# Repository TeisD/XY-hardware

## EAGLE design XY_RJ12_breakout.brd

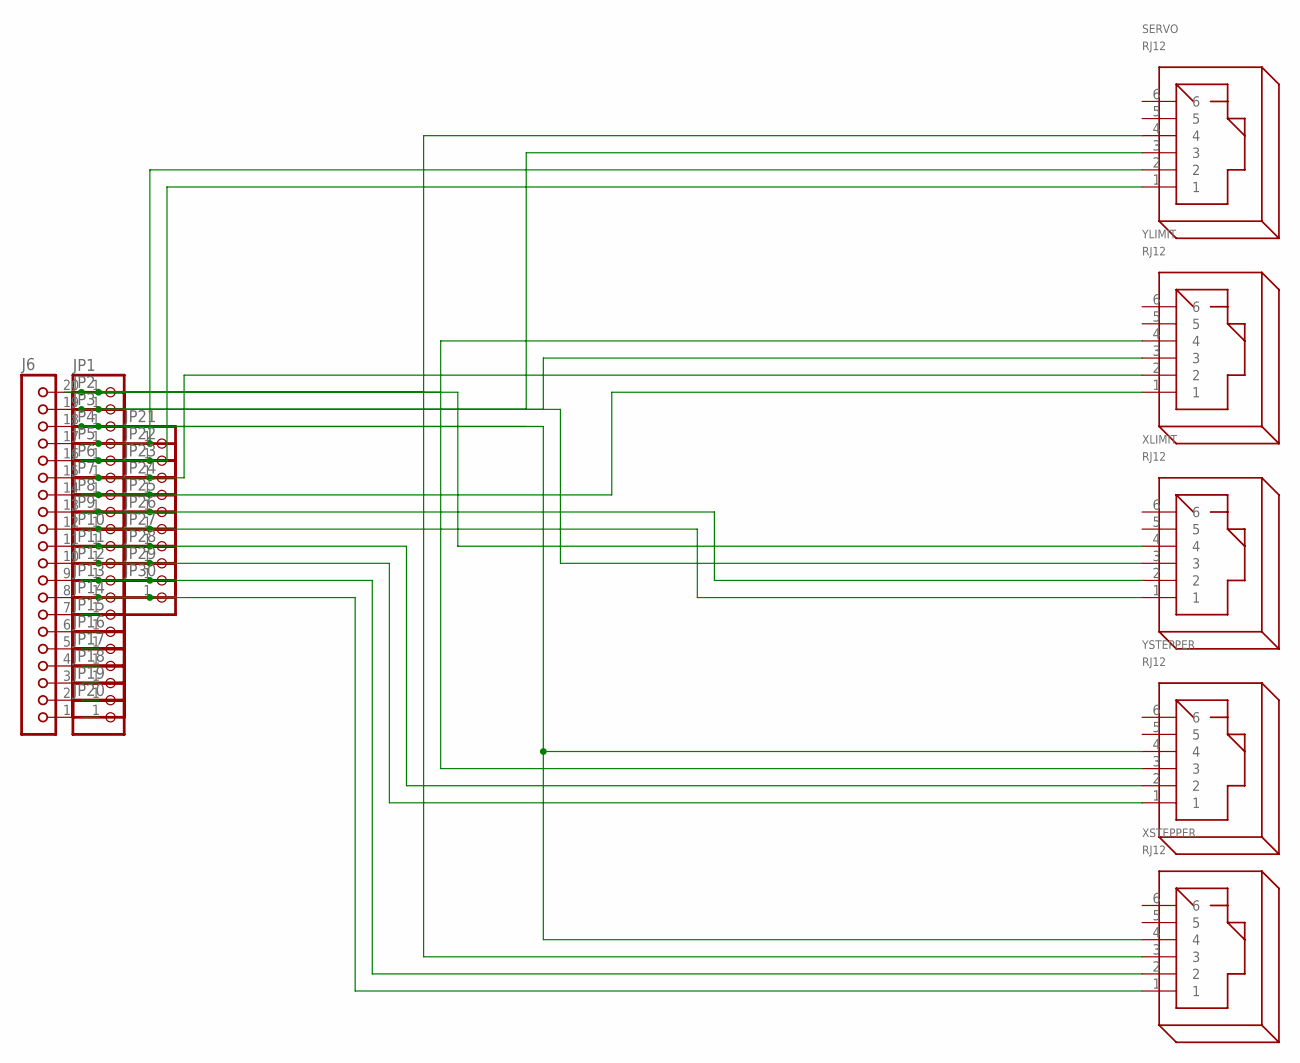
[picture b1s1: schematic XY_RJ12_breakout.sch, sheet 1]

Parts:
J6: JBK20
JP1, JP2, JP3, JP4, JP5, JP6, JP7, JP8, JP9, JP10, JP11, JP12, JP13, JP14, JP15, JP16, JP17, JP18, JP19, JP20, JP21, JP22, JP23, JP24, JP25, JP26, JP27, JP28, JP29, JP30: PINHD-1X1; 1X01
SERVO: RJ12
XLIMIT: RJ12
XSTEPPER: RJ12
YLIMIT: RJ12
YSTEPPER: RJ12

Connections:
unnamed: J6.20, JP1.1, SERVO.4, XLIMIT.4, XSTEPPER.3, YLIMIT.4, YSTEPPER.3
unnamed: J6.19, JP2.1, SERVO.3, XLIMIT.3, YLIMIT.3
unnamed: J6.18, JP3.1, XSTEPPER.4, YSTEPPER.4
unnamed: J6.17, JP4.1, JP21.1, SERVO.2
unnamed: J6.16, JP5.1, JP22.1, SERVO.1
unnamed: J6.15, JP6.1, JP23.1, YLIMIT.2
unnamed: J6.14, JP7.1, JP24.1, YLIMIT.1
unnamed: J6.13, JP8.1, JP25.1, XLIMIT.2
unnamed: J6.12, JP9.1, JP26.1, XLIMIT.1
unnamed: J6.11, JP10.1, JP27.1, YSTEPPER.2
unnamed: J6.10, JP11.1, JP28.1, YSTEPPER.1
unnamed: J6.9, JP12.1, JP29.1, XSTEPPER.2
unnamed: J6.8, JP13.1, JP30.1, XSTEPPER.1
unnamed: J6.1, JP20.1
unnamed: J6.2, JP19.1
unnamed: J6.3, JP18.1
unnamed: J6.4, JP17.1
unnamed: J6.5, JP16.1
unnamed: J6.6, JP15.1
unnamed: J6.7, JP14.1

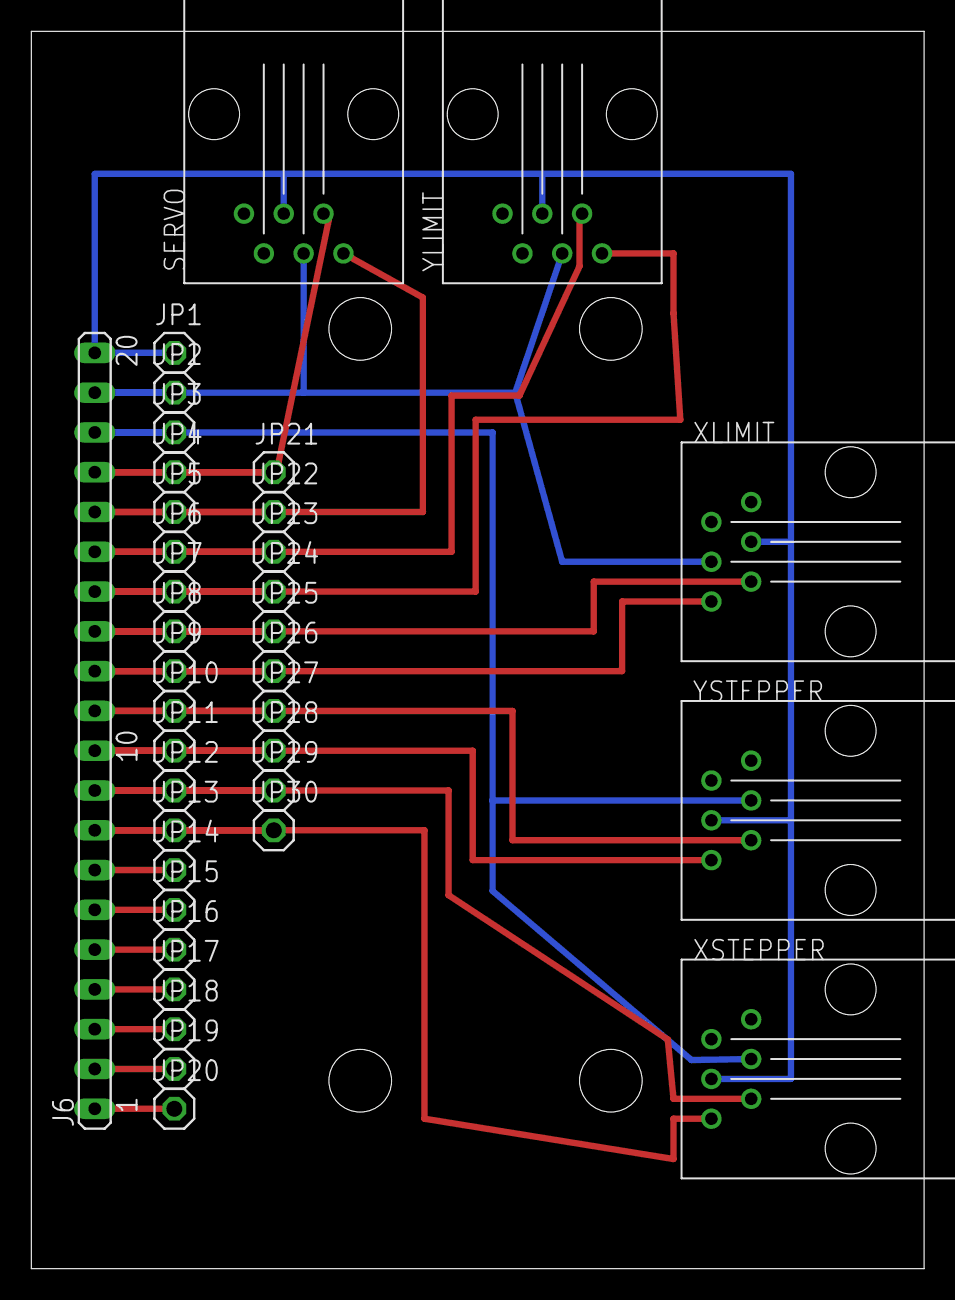
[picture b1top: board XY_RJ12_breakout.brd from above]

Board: 2 copper layers, 57.0 x 79.0 mm, 36 parts (0 on the bottom side), 20 nets.

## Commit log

2016-11-07 Add breakout board Eagle files
2016-11-07 Fix wrong label on XSTEPPER and YSTEPPER port
